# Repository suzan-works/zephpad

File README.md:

# Zephpad（ゼフパッド）

AIツールへの入力や承認操作を簡単にすることを主目的とした、自作の左手用マクロパッドです。定型文の入力や、AIが提案した処理の承認・拒否など、繰り返し行う操作を手元のキーで実行できることを目指しています。

4個のキースイッチとロータリーエンコーダを備え、Seeed Studio XIAOを使用しています。XIAO nRF52840向けのZephyrファームウェアを `software/zephpad/` に保存しています。

ケースはあくまで試作品です。  

## 確認できていること

- 4個のキースイッチ入力、ロータリーエンコーダの読み取り、インジケータLEDの点灯。
- XIAO nRF52840で、LiPoバッテリー駆動によるBLEキーボードとしての文字入力。
- ピンヘッダー接続でXIAO nRF52840とXIAO RP2040を差し替え、同じArduinoソースコードを各ボード向けにビルドしてUSBキーボードとして動作。
- バッテリープラス端子のはんだ付け、および試作ケースの組み付け。

## ファームウェア

ソースは `software/zephpad/` にあります。接続中・未接続とも無操作5分でSystem OFFし、SW4で復帰します。キー保持中とBLE接続後の暗号化・HID通知準備中はOFFしません。操作や接続状態の変化でタイマーを数え直します。Zephyr 4.4.1／Zephyr SDK v1.0.1でビルドと実機動作を確認済み。

## ハードウェア

専用の試作プリント基板に、XIAO、キースイッチ4個、ロータリーエンコーダ、LEDと電流制限抵抗を実装しています。nRF52840を使う構成ではLiPoバッテリーを接続して動作を確認しています。

## 組み立ての概要と注意点

1. 基板に各部品とXIAOをはんだ付けします。
2. nRF52840でバッテリーを使用する場合は、基板裏側の大径スルーホールからXIAO裏面のBAT＋端子を接続します。
3. USBとバッテリーを外した状態で、TP1(BAT＋)とTP2(GND)の短絡がないことを確認します。

ハンダ付けの際に、ピンヘッダーでXiaoを固定すると位置が決めやすいです。(ズレが小さくできる)

| BAT＋のはんだ付け前 | BAT＋のはんだ付け後 |
| --- | --- |
|  |  |

### はんだ付け後の短絡チェック

XIAOのはんだ付け後、USBとバッテリーを接続する前に、TP1（VBAT）とTP2（GND）が短絡していないことをテスターで確認します。

### XIAOの差し替え

ピンヘッダー接続の試作では、RP2040に差し替えてUSBキーボードとして動作を確認しています。

XIAO nRF52840とRP2040では、裏面のバッテリープラス端子を共用できません。Xiao RP2040を付けた場合は、有線USBキーボードのみの動作になります。

## 設計データ

KiCadプロジェクトは `hardware/kicad/zephpad/zephpad.kicad_pro` に配置します。

KiCanvasで設計データをブラウザから閲覧できます。

- [回路図をブラウザで見る](https://kicanvas.org/?repo=https%3A%2F%2Fgithub.com%2Fsuzan-works%2Fzephpad%2Fblob%2Fmain%2Fhardware%2Fkicad%2Fzephpad%2Fzephpad.kicad_sch)
- [基板設計ファイルをブラウザで見る](https://kicanvas.org/?repo=https%3A%2F%2Fgithub.com%2Fsuzan-works%2Fzephpad%2Fblob%2Fmain%2Fhardware%2Fkicad%2Fzephpad%2Fzephpad.kicad_pcb)

本資料は開発途中の試作記録です。バッテリー周りの安全性評価と、公開・配布に向けた条件の整理は完了していません。

## ライセンス

本リポジトリは [MIT License](LICENSE) で公開しています。

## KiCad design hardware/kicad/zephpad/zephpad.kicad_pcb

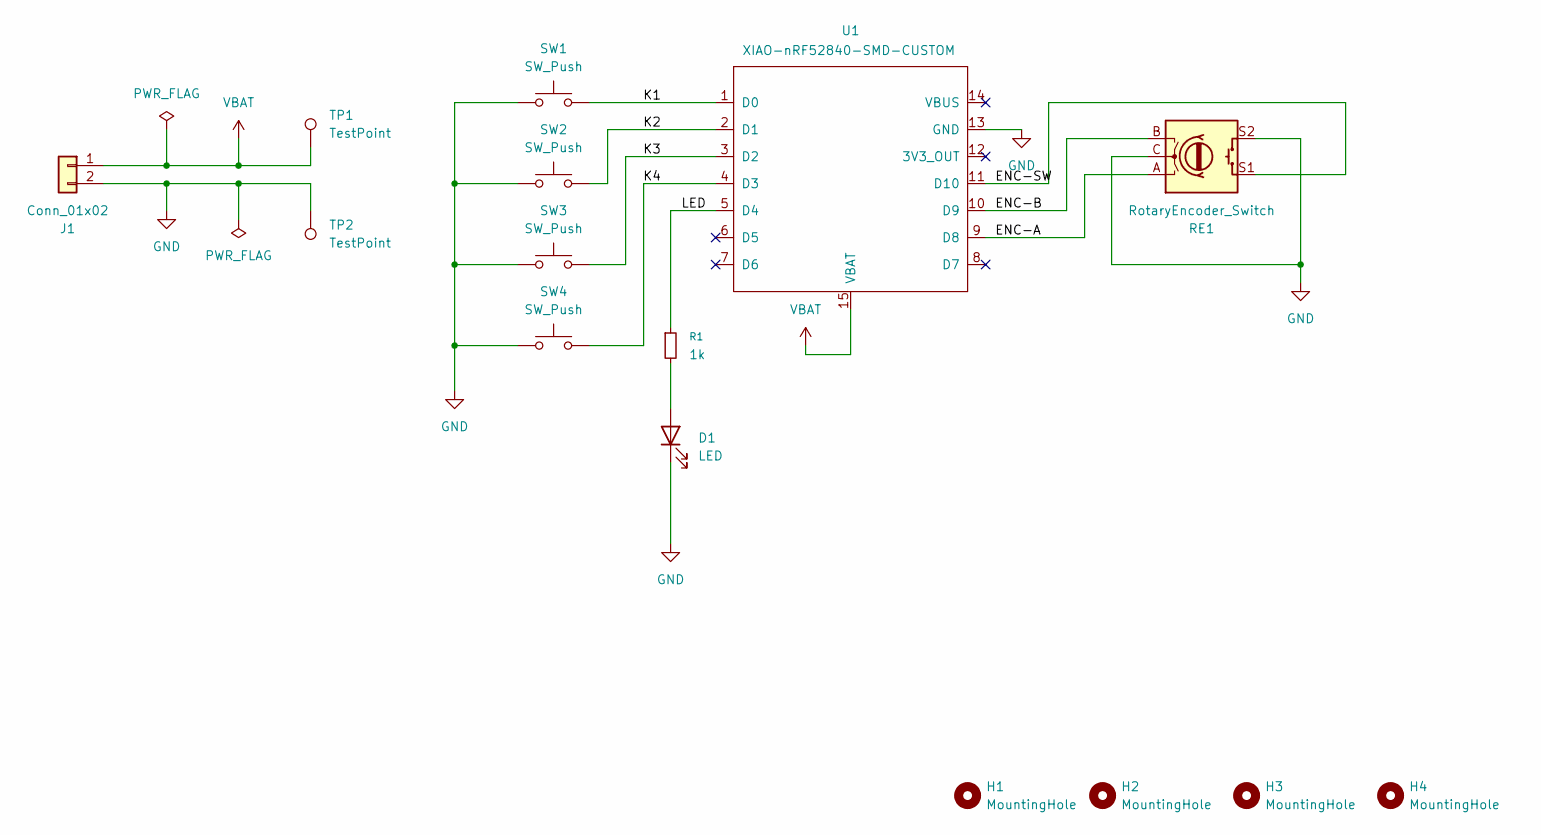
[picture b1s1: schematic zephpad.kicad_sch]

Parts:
D1: LED; LED_D3.0mm
H1, H2, H3, H4: MountingHole; MountingHole_3.2mm_M3
J1: Conn_01x02; JST_PH_S2B-PH-K_1x02_P2.00mm_Horizontal
R1: 1k; R_Axial_DIN0207_L6.3mm_D2.5mm_P10.16mm_Horizontal
RE1: RotaryEncoder_Switch; RotaryEncoder_Alps_EC12E-Switch_Vertical_H20mm
SW1, SW2, SW3, SW4: SW_Push; SW_Cherry_MX_1.00u_PCB
TP1, TP2: TestPoint; TestPoint_Pad_D1.5mm
U1: XIAO-nRF52840-SMD-CUSTOM; XIAO-nRF52840-DIP-CUSTOM

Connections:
/ENC-A: RE1.A, U1.9 (D8)
/ENC-B: RE1.B, U1.10 (D9)
/ENC-SW: RE1.S1, U1.11 (D10)
/K1: SW1.2, U1.1 (D0)
/K2: SW2.2, U1.2 (D1)
/K3: SW3.2, U1.3 (D2)
/K4: SW4.2, U1.4 (D3)
/LED: R1.1, U1.5 (D4)
GND: D1.1 (K), J1.2, RE1.C, RE1.S2, SW1.1, SW2.1, SW3.1, SW4.1, TP2.1, U1.13 (GND)
unnamed: D1.2 (A), R1.2
VBAT: J1.1, TP1.1, U1.15 (VBAT)

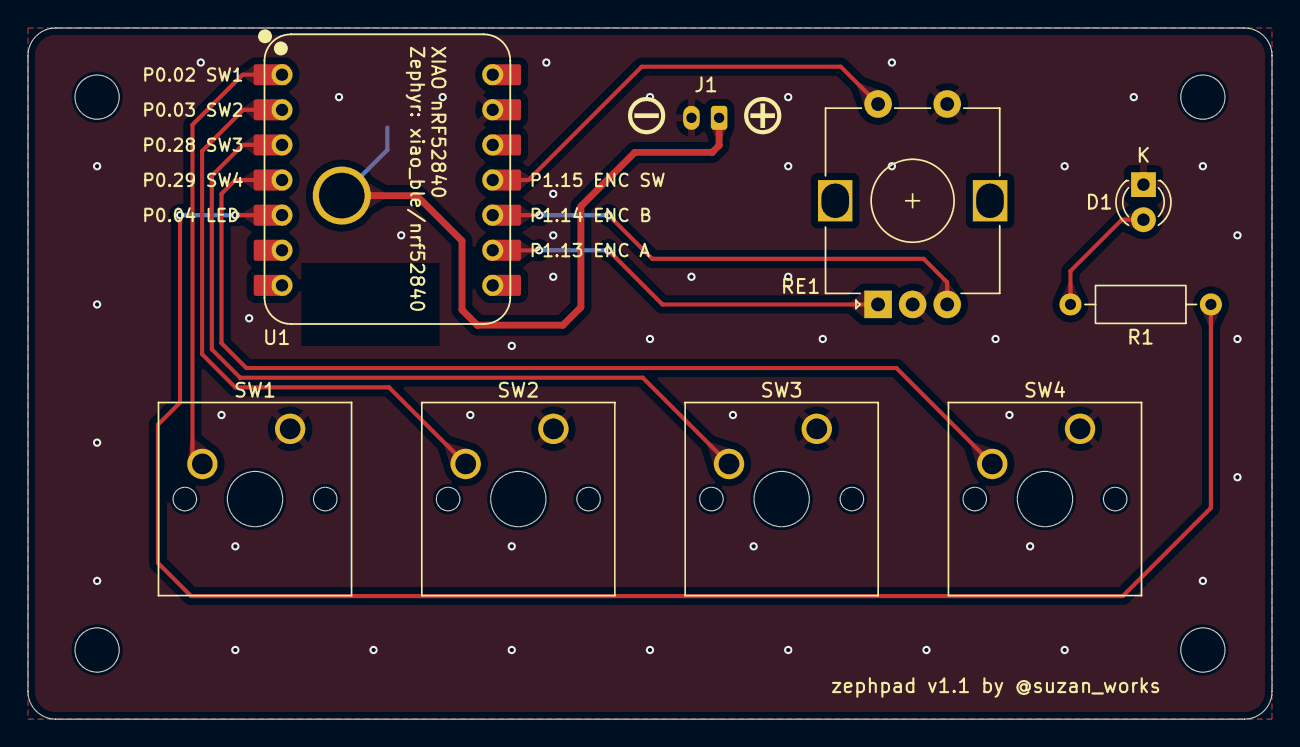
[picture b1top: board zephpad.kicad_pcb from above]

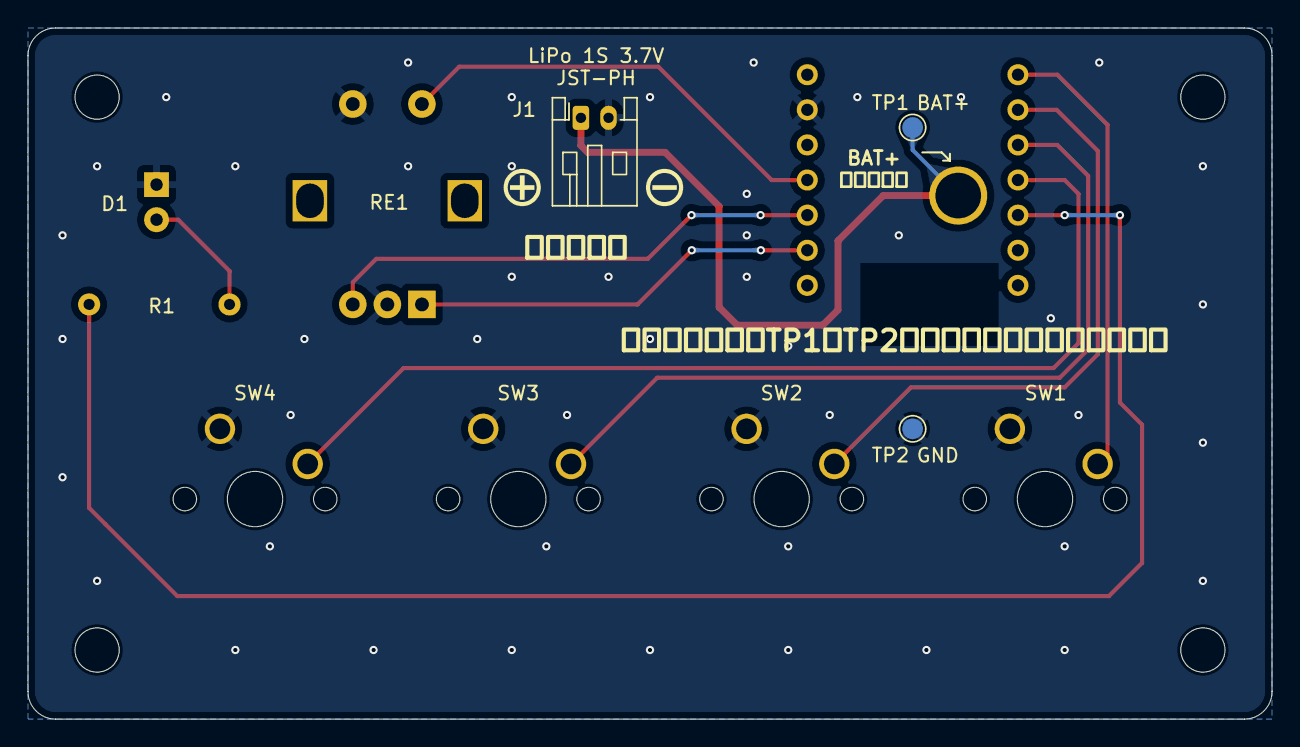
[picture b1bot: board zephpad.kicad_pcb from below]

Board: 2 copper layers, 90.0 x 50.0 mm, 15 parts (3 on the bottom side), 11 nets.
